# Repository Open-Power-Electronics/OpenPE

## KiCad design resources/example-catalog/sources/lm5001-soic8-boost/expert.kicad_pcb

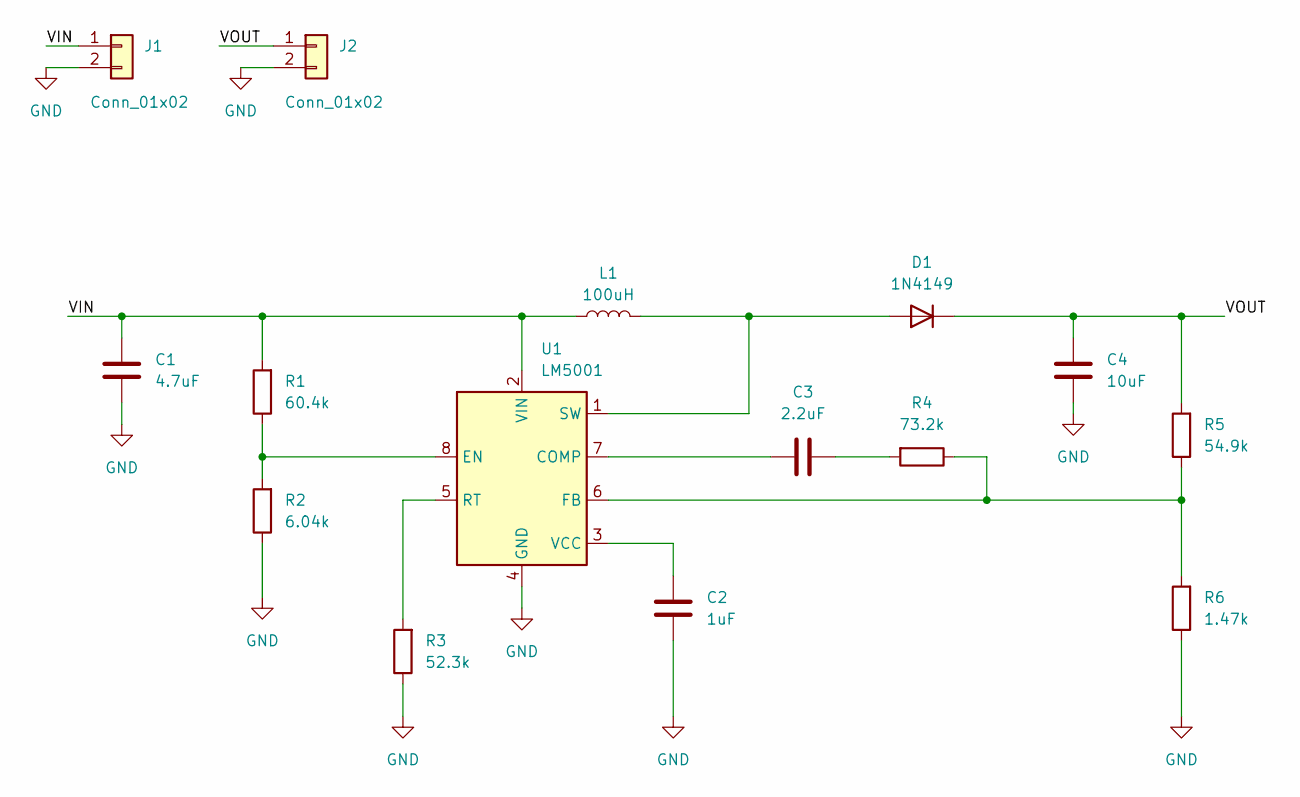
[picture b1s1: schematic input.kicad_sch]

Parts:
C1: 4.7uF; C_1206_3216Metric
C2: 1uF; C_0603_1608Metric
C3: 2.2uF; C_0603_1608Metric
C4: 10uF; C_1206_3216Metric
D1: 1N4149; D_DO-35_SOD27_P7.62mm_Horizontal
J1, J2: Conn_01x02; TerminalBlock_Phoenix_PT-1,5-2-3.5-H_1x02_P3.50mm_Horizontal
L1: 100uH; L_TDK_SLF7055
R1: 60.4k; R_0603_1608Metric
R2: 6.04k; R_0603_1608Metric
R3: 52.3k; R_0603_1608Metric
R4: 73.2k; R_0603_1608Metric
R5: 54.9k; R_0603_1608Metric
R6: 1.47k; R_0603_1608Metric
U1: LM5001; SOIC-8_3.9x4.9mm_P1.27mm

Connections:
/VIN: C1.1, J1.1, L1.1, R1.2, U1.2 (VIN)
/VOUT: C4.1, D1.1 (K), J2.1, R5.2
GND: C1.2, C2.1, C4.2, J1.2, J2.2, R2.1, R3.1, R6.1, U1.4 (GND)
unnamed: C3.1, R4.2
unnamed: D1.2 (A), L1.2, U1.1 (SW)
unnamed: C3.2, U1.7 (COMP)
unnamed: R1.1, R2.2, U1.8 (EN)
unnamed: R4.1, R5.1, R6.2, U1.6 (FB)
unnamed: R3.2, U1.5 (RT)
unnamed: C2.2, U1.3 (VCC)

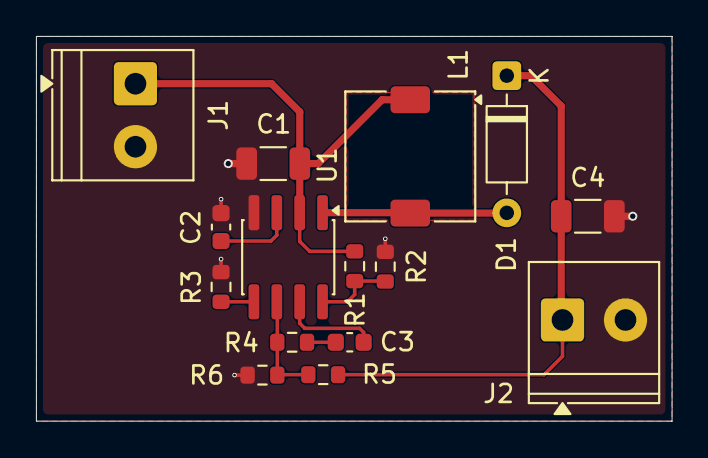
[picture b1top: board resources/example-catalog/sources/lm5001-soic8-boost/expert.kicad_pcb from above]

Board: 2 copper layers, 35.3 x 21.4 mm, 15 parts (0 on the bottom side), 10 nets.

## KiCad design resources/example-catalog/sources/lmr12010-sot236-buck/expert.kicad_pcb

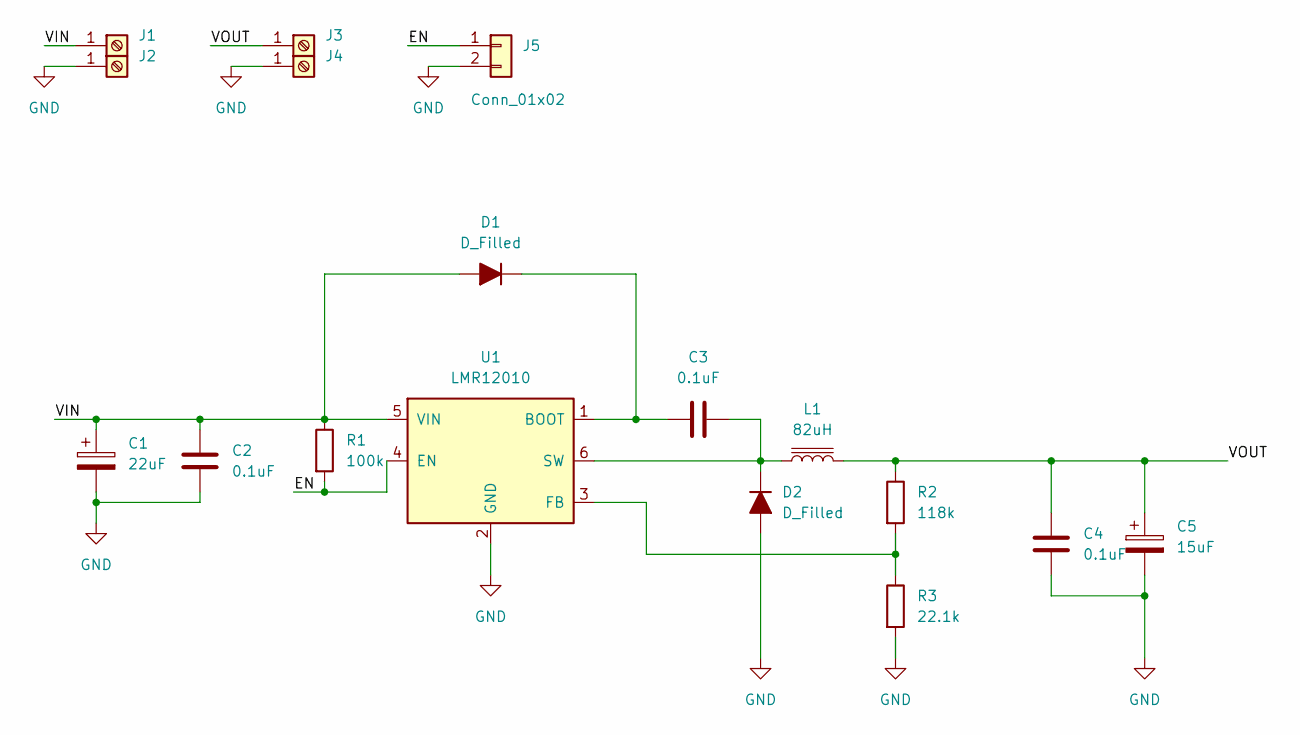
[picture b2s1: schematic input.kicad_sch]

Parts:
C1: 22uF; CP_Elec_6.3x5.3
C2, C4: 0.1uF; C_0805_2012Metric
C3: 0.1uF; C_0603_1608Metric
C5: 15uF; CP_Elec_6.3x5.3
D1: D_Filled; D_SOD-123
D2: D_Filled; D_SMA
J1, J2, J3, J4: Screw_Terminal_01x01; Wuerth_REDCUBE-THR_WP-THRSH_74651174_THR
J5: Conn_01x02; PinSocket_1x02_P2.00mm_Vertical
L1: 82uH; L_APV_APH0530
R1: 100k; R_0603_1608Metric
R2: 118k; R_0603_1608Metric
R3: 22.1k; R_0603_1608Metric
U1: LMR12010; SOT-23-6

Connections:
/EN: J5.1, R1.2, U1.4 (EN)
/VIN: C1.1, C2.2, D1.2 (A), J1.1 (Pin_1_1), R1.1, U1.5 (VIN)
/VOUT: C4.2, C5.1, J3.1 (Pin_1_1), L1.1, R2.1
GND: C1.2, C2.1, C4.1, C5.2, D2.2 (A), J2.1 (Pin_1_1), J4.1 (Pin_1_1), J5.2, R3.2, U1.2 (GND)
unnamed: C3.1, D1.1 (K), U1.1 (BOOT)
unnamed: C3.2, D2.1 (K), L1.2, U1.6 (SW)
unnamed: R2.2, R3.1, U1.3 (FB)

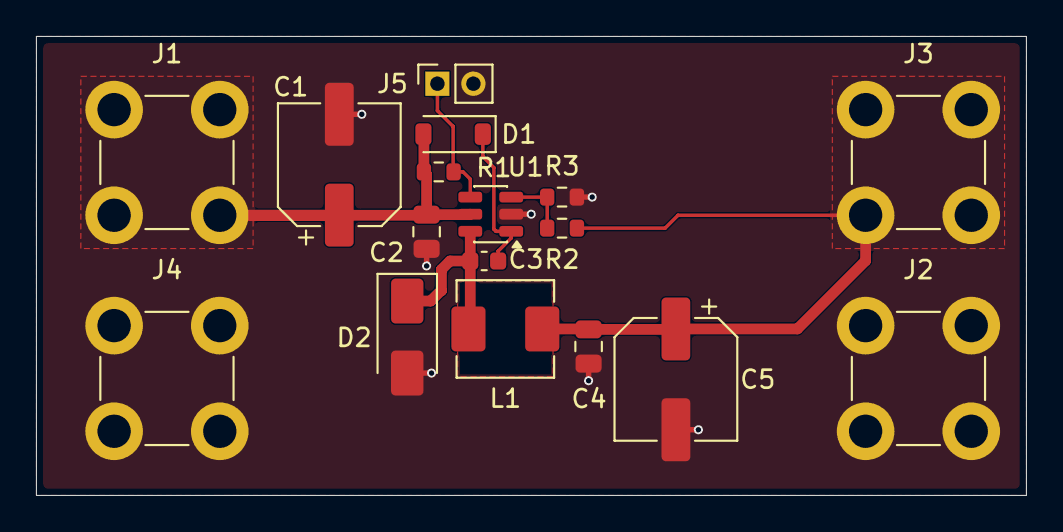
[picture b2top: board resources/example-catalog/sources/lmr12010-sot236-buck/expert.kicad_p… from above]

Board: 2 copper layers, 55.0 x 25.5 mm, 17 parts (0 on the bottom side), 7 nets.

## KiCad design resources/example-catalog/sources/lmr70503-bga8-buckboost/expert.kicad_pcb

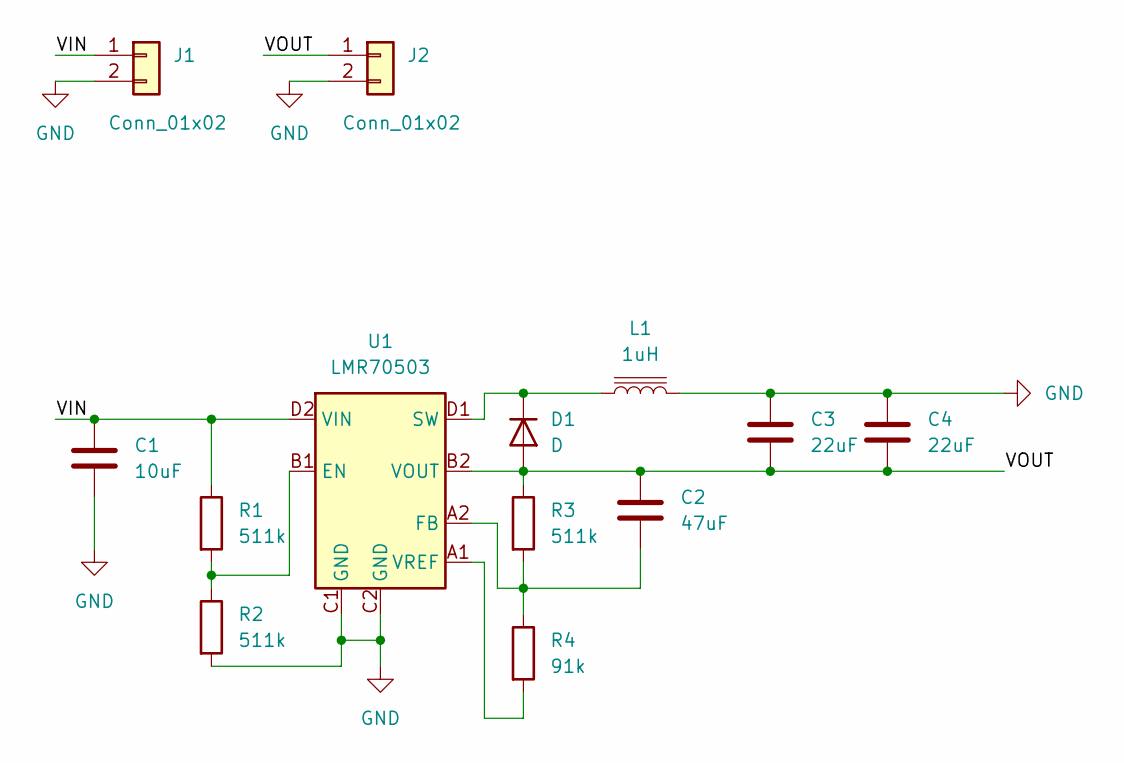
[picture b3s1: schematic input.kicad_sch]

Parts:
C1: 10uF; C_0805_2012Metric
C2: 47uF; C_0402_1005Metric
C3, C4: 22uF; C_0805_2012Metric
D1: D; D_MicroMELF
J1, J2: Conn_01x02; PinHeader_1x02_P1.27mm_Horizontal
L1: 1uH; L_Wurth_WE-LQSH-2512
R1, R2, R3: 511k; R_0402_1005Metric
R4: 91k; R_0402_1005Metric
U1: LMR70503; Texas_DSBGA-8_0.9x1.9mm_Layout2x4_P0.5mm

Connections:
/VIN: C1.1, J1.1, R1.1, U1.D2 (VIN)
/VOUT: C2.2, C3.1, C4.1, D1.2 (A), J2.1, R3.1, U1.B2 (VOUT)
GND: C1.2, C3.2, C4.2, J1.2, J2.2, L1.2, R2.2, U1.C1 (GND), U1.C2 (GND)
unnamed: D1.1 (K), L1.1, U1.D1 (SW)
unnamed: R1.2, R2.1, U1.B1 (EN)
unnamed: C2.1, R3.2, R4.1, U1.A2 (FB)
unnamed: R4.2, U1.A1 (VREF)

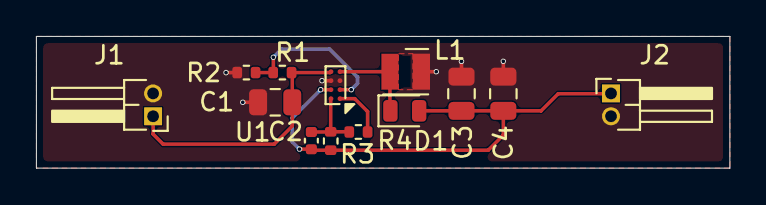
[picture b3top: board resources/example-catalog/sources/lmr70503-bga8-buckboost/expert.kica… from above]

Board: 2 copper layers, 38.5 x 7.3 mm, 13 parts (0 on the bottom side), 7 nets.

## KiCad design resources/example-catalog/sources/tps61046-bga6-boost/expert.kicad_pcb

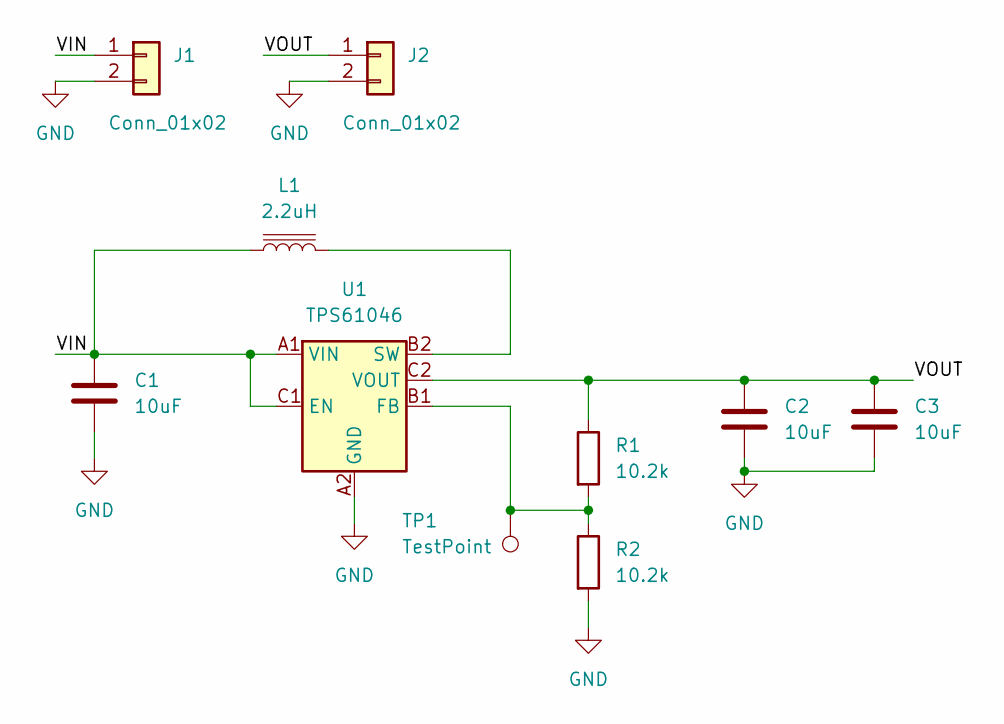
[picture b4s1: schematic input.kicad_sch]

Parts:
C1, C2, C3: 10uF; C_0603_1608Metric
J1, J2: Conn_01x02; PinHeader_1x02_P2.00mm_Vertical
L1: 2.2uH; L_Wurth_WE-LQSH-2010
R1, R2: 10.2k; R_0603_1608Metric
TP1: TestPoint; TestPoint_Keystone_5005-5009_Compact
U1: TPS61046; Texas_DSBGA-6_0.855x1.255mm_Layout2x3_P0.4mm_LevelC

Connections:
/VIN: C1.1, J1.1, L1.1, U1.A1 (VIN), U1.C1 (EN)
/VOUT: C2.2, C3.2, J2.1, R1.1, U1.C2 (VOUT)
GND: C1.2, C2.1, C3.1, J1.2, J2.2, R2.2, U1.A2 (GND)
unnamed: R1.2, R2.1, TP1.1 (1_1), U1.B1 (FB)
unnamed: L1.2, U1.B2 (SW)

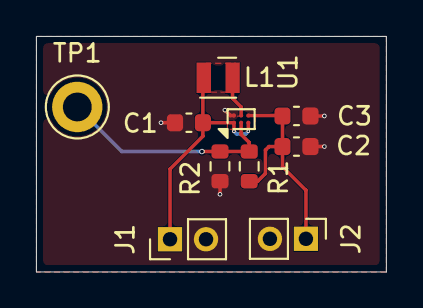
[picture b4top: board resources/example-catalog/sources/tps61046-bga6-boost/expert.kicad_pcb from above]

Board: 2 copper layers, 19.4 x 13.1 mm, 10 parts (0 on the bottom side), 5 nets.

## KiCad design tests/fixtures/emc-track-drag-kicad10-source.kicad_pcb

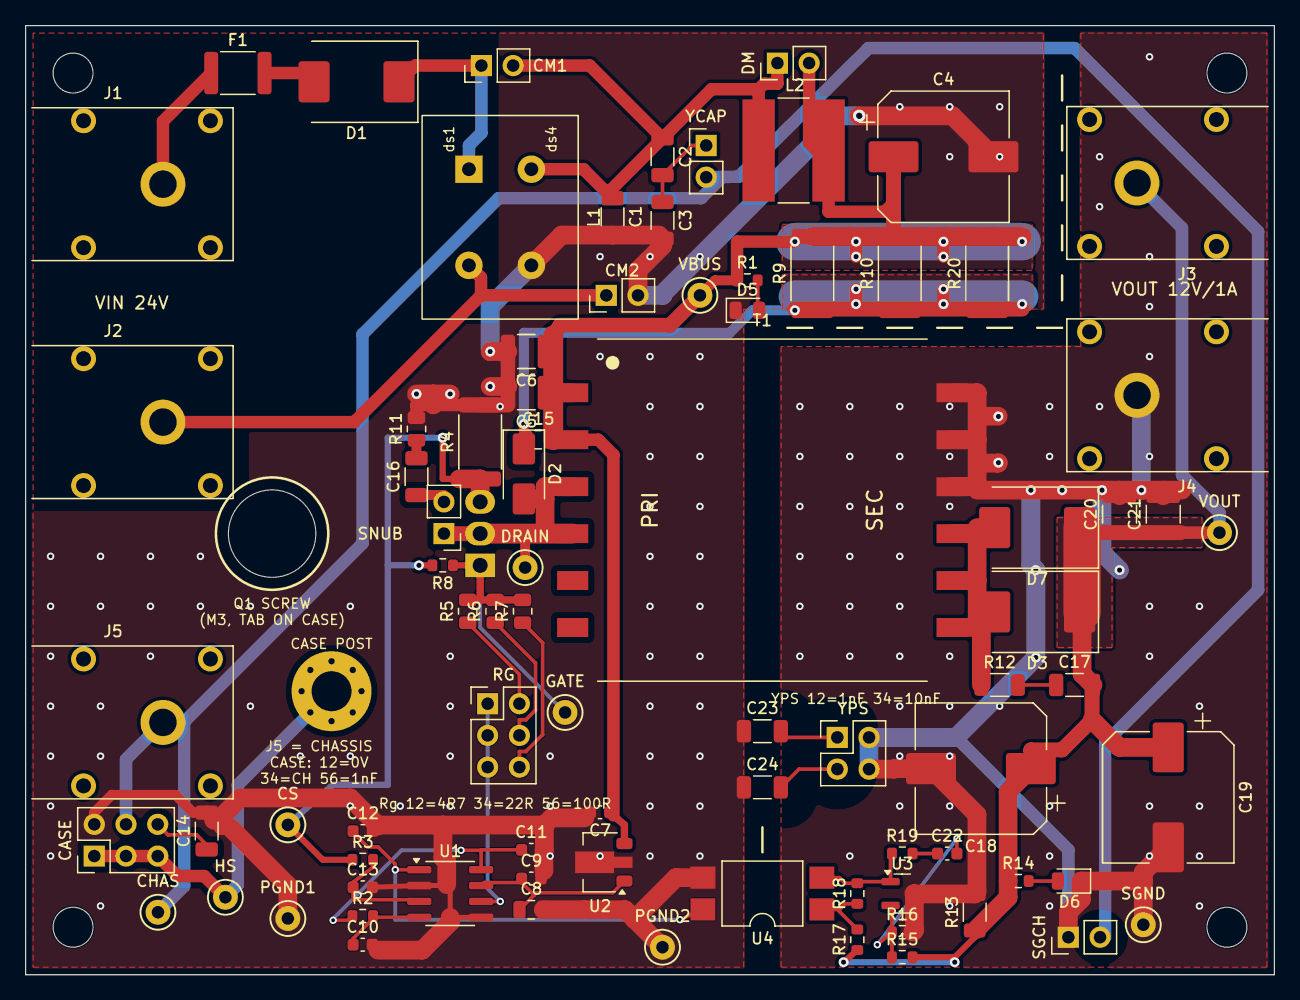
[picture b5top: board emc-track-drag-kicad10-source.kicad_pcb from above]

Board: 2 copper layers, 100.0 x 76.0 mm, 90 parts (0 on the bottom side), 38 nets.

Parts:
C1: 1u; C_1206_3216Metric
C2, C3, C24: 10n; C_1206_3216Metric
C4: 100u; CP_Elec_10x10
C5, C6: 4.7u; C_1210_3225Metric
C7, C9, C11: 100n; C_0603_1608Metric
C8: 10u; C_0805_2012Metric
C10, C12: 1n; C_0603_1608Metric
C13: 220p; C_0603_1608Metric
C14, C23: 1n; C_1206_3216Metric
C15: 22n; C_0805_2012Metric
C16, C17: 100p; C_1206_3216Metric
C18, C19: 470u; CP_Elec_10x10
C20, C21: 22u; C_1210_3225Metric
C22: 47n; C_0603_1608Metric
CASE: Case select; PinHeader_2x03_P2.54mm_Vertical
CHAS: CHASSIS; TestPoint_Keystone_5000-5004_Miniature
CM1: CM bypass +; PinHeader_1x02_P2.54mm_Vertical
CM2: CM bypass -; PinHeader_1x02_P2.54mm_Vertical
CS: CSRAW; TestPoint_Keystone_5000-5004_Miniature
D1, D3, D7: SS510C; D_SMC
D2: ES2D; D_SMA
D5: RED; LED_0805_2012Metric
D6: GREEN; LED_0805_2012Metric
DM: DM bypass; PinHeader_1x02_P2.54mm_Vertical
DRAIN: SW; TestPoint_Keystone_5000-5004_Miniature
F1: 2A/30V PTC; Fuse_1812_4532Metric
GATE: GATE; TestPoint_Keystone_5000-5004_Miniature
HS: HS; TestPoint_Keystone_5000-5004_Miniature
J1: VIN+ 24V; Jack_4mm_RA_Cliff_FCR7350
J2: VIN- 0V; Jack_4mm_RA_Cliff_FCR7350
J3: VOUT +12V; Jack_4mm_RA_Cliff_FCR7350
J4: VOUT 0V; Jack_4mm_RA_Cliff_FCR7350
J5: CHASSIS; Jack_4mm_RA_Cliff_FCR7350
L1: 2.2mH; L_CommonMode_Wuerth_WE-CMB-S_744822222
L2: 10uH; L_Bourns-SRN8040_8x8.15mm
MECH1: Case_UChannel_revD
MECH2: Cover_PMMA_revD
MH1, MH2, MH3, MH4: M3; MountingHole_3.2mm_M3
MH5: M3 CASE; MountingHole_3.2mm_M3_Pad_Via
PGND1, PGND2: PGND; TestPoint_Keystone_5000-5004_Miniature
Q1: IRF520NPBF; TO-220-3_BottomMount_CaseHeatsink
R1, R8, R16, R19: 10k; R_0603_1608Metric
R2: 5.6k; R_0603_1608Metric
R3, R17, R18: 1k; R_0603_1608Metric
R4: 0.15R; R_2512_6332Metric
R5: 4.7R; R_0805_2012Metric
R6: 22R; R_0805_2012Metric
R7: 100R; R_0805_2012Metric
R9, R10, R20: 4.7k; R_2512_6332Metric
R11: 47R; R_0805_2012Metric
R12: 10R; R_1206_3216Metric
R13: 1k; R_1206_3216Metric
R14: 4.7k; R_0603_1608Metric
R15: 39k; R_0603_1608Metric
RG: Rg select; PinHeader_2x03_P2.54mm_Vertical
SGCH: SGND to chassis; PinHeader_1x02_P2.54mm_Vertical
SGND: SGND; TestPoint_Keystone_5000-5004_Miniature
SNUB: RC snubber on; PinHeader_1x02_P2.54mm_Vertical
T1: 750311591; Wurth_750311591_EFD25
U1: UC3845B; SOIC-8_3.9x4.9mm_P1.27mm
U2: L78L12ACUTR; SOT-89-3
U3: TL431AIDBZR; SOT-23
U4: LTV-817S; SMDIP-4_W9.53mm
VBUS: VBUS; TestPoint_Keystone_5000-5004_Miniature
VOUT: VOUT; TestPoint_Keystone_5000-5004_Miniature
YCAP: Y-caps to chassis; PinHeader_1x02_P2.54mm_Vertical
YPS: Pri-sec Y-cap; PinHeader_2x02_P2.54mm_Vertical

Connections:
CHASSIS: CASE.4, CHAS.1, J5.1, SGCH.2, YCAP.2
CLAMP: C15.1, D2.1, R9.1, R10.1, R20.1
COMP: C12.1, U1.1, U4.4
CSRAW: CS.1, Q1.3, R3.1, R4.1, R8.2
DRV: RG.1, RG.3, RG.5, U1.6
FBC: C22.1, R19.2
FBK: R18.2, R19.1, U3.1, U4.2
FP: C1.1, C2.1, CM1.2, DM.1, L1.2, L2.1
GATE: GATE.1, Q1.1, R5.2, R6.2, R7.2, R8.1
HS: CASE.1, CASE.3, CASE.5, HS.1, MH5.1
HSY: C14.1, CASE.6
ISENSE: C13.1, R3.2, U1.3
LEDP: D5.2, R1.2
LEDS: D6.2, R14.2
OPTA: R17.2, R18.1, U4.1
PGND: C1.2, C3.2, C4.2, C5.2, C6.2, C7.2, C8.2, C9.2, C10.2, C11.2, C12.2, C13.2, C14.2, C23.1, C24.1, CASE.2, CM2.2, D5.1, L1.4, PGND1.1, PGND2.1, R4.2, R11.2, U1.2, U1.5, U2.2, U4.3
PSY1: C23.2, YPS.1
PSY2: C24.2, YPS.3
REF: C22.2, R15.2, R16.1, U3.2
RG1: R5.1, RG.2
RG2: R6.1, RG.4
RG3: R7.1, RG.6
RTCT: C10.1, R2.2, U1.4
SEC: D3.2, D7.2, R12.1, T1.7, T1.8, T1.9
SGND: C18.2, C19.2, C20.2, C21.2, D6.1, J4.1, R13.2, R16.2, SGCH.1, SGND.1, T1.10, T1.11, T1.12, U3.3, YPS.2, YPS.4
SNA: C16.1, SNUB.2
SNB: C16.2, R11.1
SNS: C17.1, R12.2
SW: D2.2, DRAIN.1, Q1.2, SNUB.1, T1.3, T1.4
VBUS: C4.1, C5.1, C6.1, C7.1, C15.2, DM.2, L2.2, R1.1, R9.2, R10.2, R20.2, T1.1, T1.2, U2.3, VBUS.1
VCC: C8.1, C9.1, U1.7, U2.1
VD: CM1.1, D1.1, L1.1
VF: D1.2, F1.2
VIN_N: CM2.1, J2.1, L1.3
VIN_P: F1.1, J1.1
VOUT: C17.2, C18.1, C19.1, C20.1, C21.1, D3.1, D7.1, J3.1, R13.1, R14.1, R15.1, R17.1, VOUT.1
VREF: C11.1, R2.1, U1.8
YN: C2.2, C3.1, YCAP.1

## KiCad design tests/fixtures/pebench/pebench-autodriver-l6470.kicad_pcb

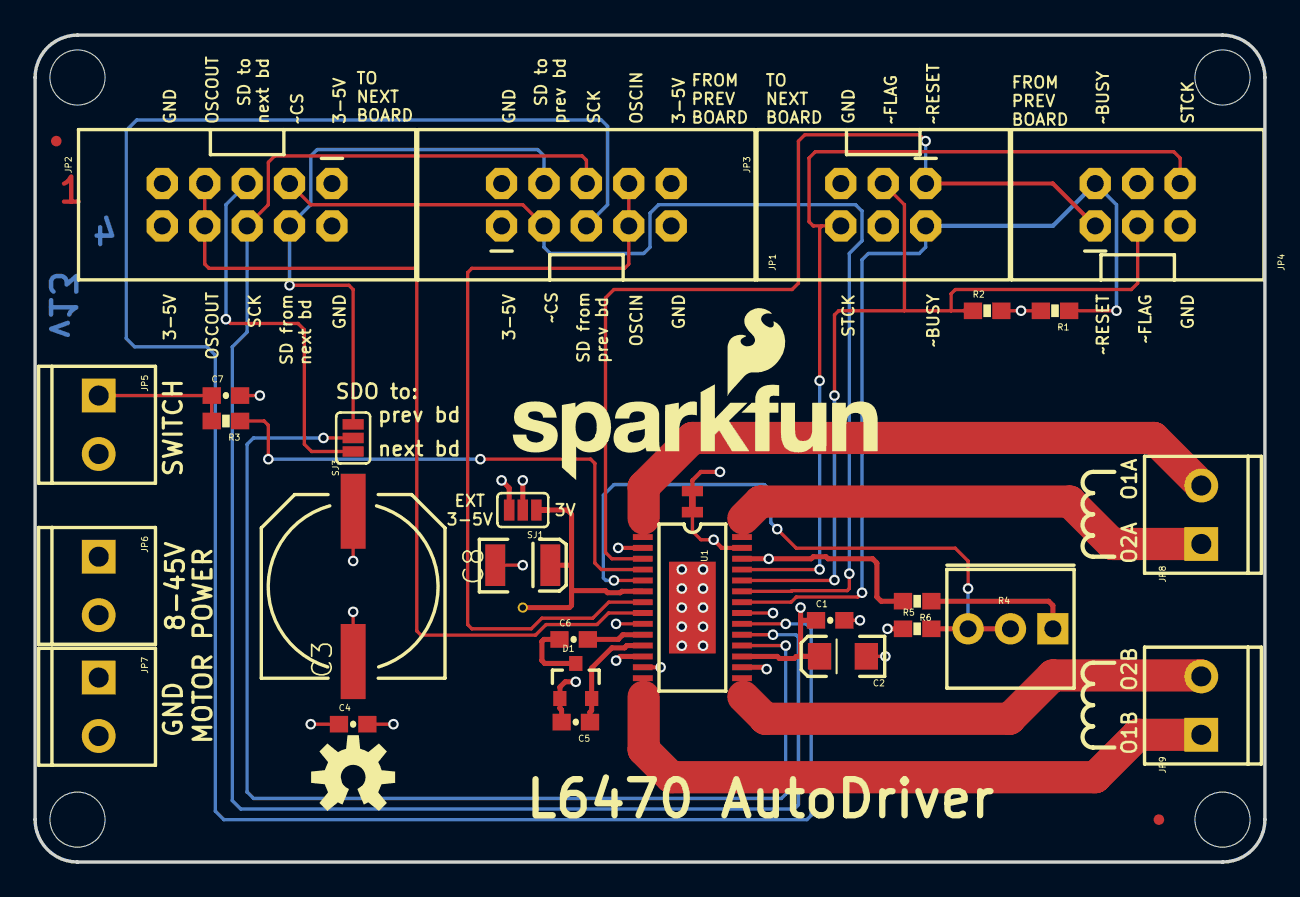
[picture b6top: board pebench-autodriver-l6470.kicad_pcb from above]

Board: 4 copper layers, 73.7 x 49.5 mm, 39 parts (0 on the bottom side), 29 nets.

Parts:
C1: 0.1uF; 0603-CAP
C2: 10uF; EIA3216
C3: 100uF; NIC_10X10.5_CAP
C4, C5: 0.22uF; 0603-CAP
C6, C7: 10nF; 0603-CAP
C8: 47uF; EIA3528
D1: BAV99; SOT23-3
FID1, FID2: FIDUCIALUFIDUCIAL; MICRO-FIDUCIAL
FRAME1: FRAME-LETTER; CREATIVE_COMMONS
JP1, JP2: M05X2SHD; 2X5-SHROUDED
JP3, JP4: M03X2SHROUD; 2X3-SHROUDED
JP5, JP6, JP7, JP8, JP9: M023.5MM; SCREWTERMINAL-3.5MM-2
LOGO1: OSHW-LOGOM; OSHW-LOGO-M
LOGO2: SFE_LOGO_NAME_FLAME.2_INCH; SFE_LOGO_NAME_FLAME_.2
R1, R2: 10k; 0603-RES
R3: 100; 0603-RES
R4: 200k; 3362U
R5: 8.2k; 0603-RES
R6: 33k; 0603-RES
SJ1, SJ3: JUMPER-PAD-3-2OF3_NC_BY_PASTE; PAD-JUMPER-3-2OF3_NC_BY_PASTE_YES_SILK_FULL_BOX
SJ2: 2PT_GND_TIE
STANDOFF1, STANDOFF2, STANDOFF3, STANDOFF4: STAND-OFF
TP1: TEST-POINTTP_15TH_THRU; TP_15TH
U1: L6470; HTSSOP28
U$4: FOUR_LAYER_WARNING

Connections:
3.3V: C8.A, SJ1.1, TP1.P$1, U1.6
5V: JP1.1, JP1.10, JP2.1, JP2.10, SJ1.3
ADC: R4.P$2, R4.P$3, R5.2, U1.5
BUSYN: JP3.2, JP4.2, R1.1, U1.22
CP_HIGH: C6.1, D1.3
CSN: JP1.3, JP2.3, U1.23
D_RETURN: JP1.4, JP2.4, SJ3.3
FLAGN: JP3.3, JP4.3, R2.1, U1.24
GND: C1.2, C2.C, C7.2, C8.C, JP1.2, JP1.9, JP2.2, JP2.9, JP3.5, JP4.5, JP5.2, R5.1, SJ2.P$1, U1.9, U1.21
unnamed: R4.P$1, R6.1
OSCIN: JP1.7, JP1.8, U1.7
OSCOUT: JP2.7, JP2.8, U1.8
OUT1A: JP8.2, U1.1
OUT1B: JP9.1, U1.14
OUT2A: JP8.1, U1.28
OUT2B: JP9.2, U1.15
PGND: C3.-, C4.2, JP7.1, JP7.2, SJ2.P$2, U1.13, U1.27, U1.29
RESETN: JP3.1, JP4.1, U1.3
SCK: JP1.6, JP2.6, U1.19
SDI: JP1.5, U1.20
SDO: SJ3.2, U1.18
SDO_DOWNSTREAM: JP2.5, SJ3.1
STCK: JP3.6, JP4.6, U1.25
SWITCH_INPUT: C7.1, JP5.1, R3.2
SWITCH_SIG: R3.1, U1.4
VLOGIC: C1.1, C2.A, R1.2, R2.2, SJ1.2, U1.17
VS: C3.+, C4.1, C5.2, D1.1, JP6.1, JP6.2, R6.2, U1.2, U1.12, U1.16, U1.26
V_BOOT: C5.1, D1.2, U1.11
V_CP: C6.2, U1.10

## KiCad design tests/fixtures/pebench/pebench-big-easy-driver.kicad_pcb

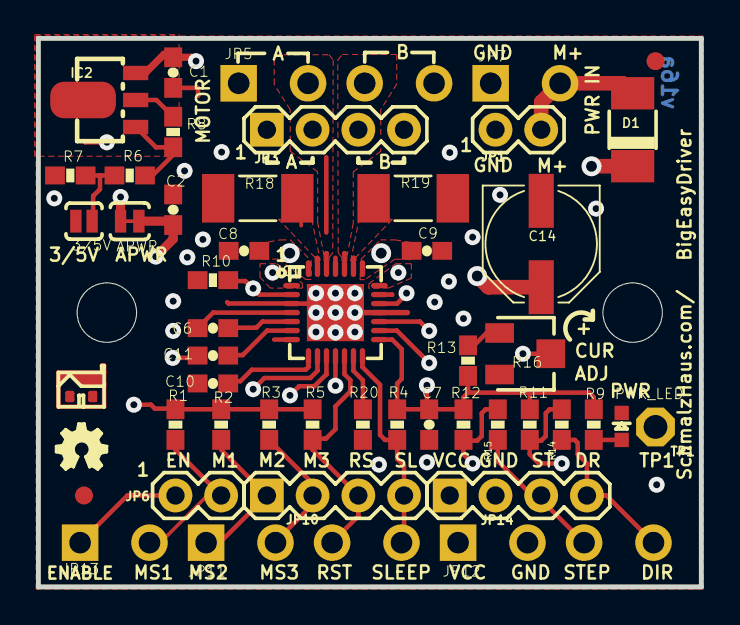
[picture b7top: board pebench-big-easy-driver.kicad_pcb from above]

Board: 4 copper layers, 36.8 x 30.5 mm, 56 parts (1 on the bottom side), 34 nets.

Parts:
3/5V: SOLDERJUMPERNO; SJ_2S-NO
APWR: SOLDERJUMPERTRACE; SJ_2S-TRACE
C1: .1uF; 0603-CAP
C2: 1uF; 0603-CAP
C6, C7, C8, C9, C11: .1uf; 0603-CAP
C10: .22uF; 0603-CAP
C14: 47uF; PANASONIC_D
D1: B340A-13-F; DO-214AC
FID1, FID2: FIDUCIAL1X2; FIDUCIAL-1X2
FRAME1: FRAME-LETTER; CREATIVE_COMMONS
IC1: A4988ALT1; QFN-28-5MM_ALT1
IC2: LM317L; SCHMALZHAUS_SOT89
JP1, JP6: M02PTH; 1X02
JP3, JP10, JP14: M04PTH; 1X04
JP5, JP11, JP12: M04SCREW_LOCK; SCREWTERMINAL-3.5MM-4_LOCK
JP7, JP13: M023.5MM_LOCK; SCREWTERMINAL-3.5MM-2_LOCK
JP8, JP9: STAND-OFF
LOGO1: OSHW_LOGO_FILLX0100-NT; OSHW_FILLX100_NOTEXT
PWR_LED: YELLOW; LED-0603
R1, R2, R3, R4, R5, R10, R11, R12, R20: 20K; 0603-RES
R6: 390; 0603-RES
R7: 330; 0603-RES
R8: 240; 0603-RES
R9, R14, R15: 1K; 0603-RES
R13: 8.2K; 0603-RES
R16: 10K; TRIMPOT-3MM-2
R18, R19: .11; R2010
TP1: TPPAD1-13; P1-13
U$1: SCHMALZHAUS_SMALL
U$2: LOGO-SFENEW; SFE-NEW-WEBLOGO
U$3, U$4, U$5: PAD; PAD-0.008

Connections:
5V_ALT: APWR.1, IC2.OUT, IC2.OUT@1, R8.2
COILA+: IC1.P$21, JP3.4, JP5.4
COILA-: IC1.P$24, JP3.3, JP5.3
COILB+: IC1.P$1, JP3.1, JP5.1
COILB-: IC1.P$26, JP3.2, JP5.2
CUR_REF: IC1.P$17, R16.2, TP1.TP
DIR: IC1.P$19, R11.1, R14.2
DIR_IN: JP12.4, JP14.4, R14.1
ENABLE: IC1.P$2, JP6.1, JP13.1, R10.1
GND: 3/5V.2, C1.2, C2.2, C7.2, C8.2, C9.2, C10.2, C14.-, IC1.P$3, IC1.P$18, IC1.P$29, JP1.1, JP7.1, JP12.2, JP14.2, PWR_LED.C, R7.1, R10.2, R16.3, R18.1, R19.1, R20.2
MS1: IC1.P$9, JP6.2, JP13.2, R1.1
MS2: IC1.P$10, JP10.1, JP11.1, R2.1
MS3: IC1.P$11, JP10.2, JP11.2, R3.1
unnamed: D1.A, JP1.2, JP7.2
unnamed: PWR_LED.A, R9.1
unnamed: R13.2, R16.1
unnamed: 3/5V.1, R6.1, R7.2
unnamed: IC1.P$7, U$3.P$1
unnamed: IC2.ADJ, R6.2, R8.1
unnamed: IC1.P$20, U$4.P$1
unnamed: C6.1, IC1.P$4
unnamed: C6.2, IC1.P$5
unnamed: IC1.P$25, U$5.P$1
unnamed: IC1.P$13, R20.1
unnamed: C10.1, IC1.P$8
unnamed: C11.1, IC1.P$6
unnamed: IC1.P$27, R18.2
unnamed: IC1.P$23, R19.2
RESET: IC1.P$12, JP10.3, JP11.3, R5.1
SLEEP: IC1.P$14, JP10.4, JP11.4, R4.1
STEP: IC1.P$16, R12.1, R15.2
STEP_IN: JP12.3, JP14.3, R15.1
V+: C1.1, C8.1, C9.1, C11.2, C14.+, D1.C, IC1.P$22, IC1.P$28, IC2.IN
VCC: APWR.2, C2.1, C7.1, IC1.P$15, JP12.1, JP14.1, R1.2, R2.2, R3.2, R4.2, R5.2, R9.2, R11.2, R12.2, R13.1

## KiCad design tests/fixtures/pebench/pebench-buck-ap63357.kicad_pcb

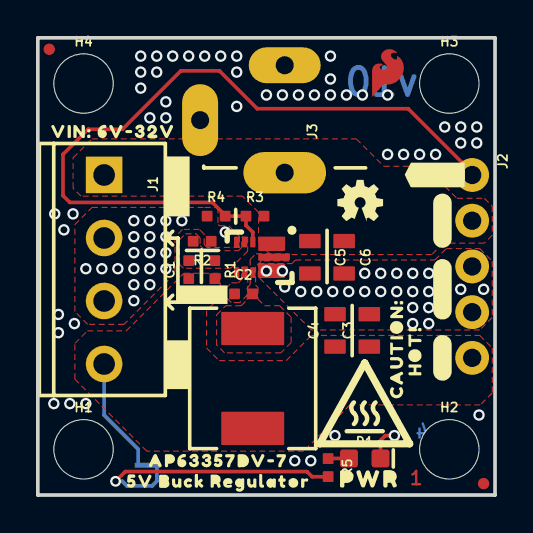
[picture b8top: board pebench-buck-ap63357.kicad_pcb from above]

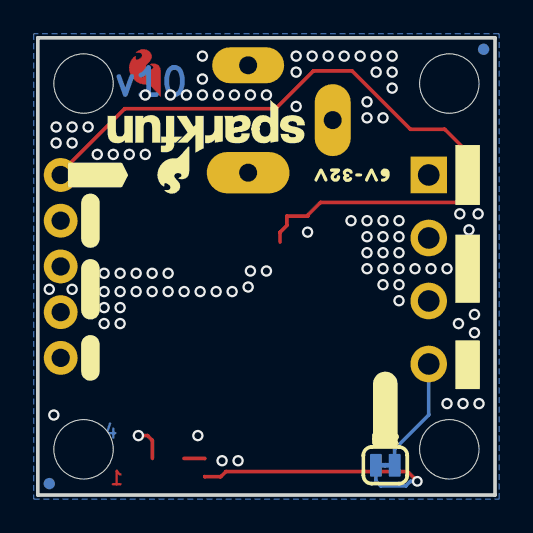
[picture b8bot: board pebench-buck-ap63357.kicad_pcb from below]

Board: 4 copper layers, 25.4 x 25.4 mm, 54 parts (13 on the bottom side), 9 nets.

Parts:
C1: 47pF; 0402-TIGHT
C2: 0.1uF; 0402-TIGHT
C3, C4: 22uF; 0805
C5, C6: 4.7uF; 0805
D1: RED; LED-0603
FD1, FD2, FD3, FD4: FIDUCIALUFIDUCIAL; FIDUCIAL-MICRO
FRAME1: FRAME-LEDGER; CREATIVE_COMMONS
H1, H2, H3, H4: STAND-OFF
J1: CONN_04SCREW; SCREWTERMINAL-3.5MM-4
J2: CONN_05NO_SILK; 1X05_NO_SILK
J3: POWER_JACK; POWER_JACK_PTH_SLOT_NO_OVRHNG_SILK
L1: 6.8UH; 07A7_6U8H
LOGO1: OSHW-LOGOMINI; OSHW-LOGO-MINI
LOGO2: SFE_LOGO_NAME_FLAME.1_INCH; SFE_LOGO_NAME_FLAME_.1
PWR: JUMPER-SMT_2_NC_TRACE_SILK; SMT-JUMPER_2_NC_TRACE_SILK
R1: 220K; 0402-TIGHT
R2: 41.2K; 0402-TIGHT
R3: 93.1k; 0402-TIGHT
R4: 22k; 0402-TIGHT
R5: 2.2k; 0402-TIGHT
U1: AP63357; V-DFN3020-13
U$1: AP63357DV#70
U$2: 5V_BUCK_REGULATOR0
U$3: #5V#4
U$4: #VIN#8
U$5, U$13: #VIN#0
U$6, U$7: #GND#0
U$8, U$19: #EN_#0
U$9: #GND#9
U$10: #5V#10
U$11: 6V#32V10
U$12: HOT##0
U$14, U$24: #5V#0
U$15: #LED_#0
U$16: CAUTION#0
U$17: SFE_LOGO_FLAME_COPPER_EXPOSED_.1
U$18: VIN#_6V#32V0
U$20: PWR0
U$21: #GND#1
U$22: HIGH_TEMP_WARNING
U$23: ORDERING_INSTRUCTIONS
U$26: #VIN#3

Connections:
5V: C1.1, C3.1, C4.1, J1.4, J2.5, L1.P$2, PWR.2, R1.2
EN: J2.1, R3.1, R4.2, U1.P$2
FB: C1.2, R1.1, R2.2, U1.P$3
GND: C3.2, C4.2, C5.2, C6.2, D1.C, J1.2, J1.3, J2.3, J2.4, J3.GND, R2.1, R4.1, U1.P$4, U1.P$8
unnamed: D1.A, R5.1
unnamed: C2.1, U1.P$6
unnamed: PWR.1, R5.2
SW: C2.2, L1.P$1, U1.P$7, U1.P$9
VIN: C5.1, C6.1, J1.1, J2.2, J3.PWR, R3.2, U1.P$1

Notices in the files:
parts and their libraries:
Released under the Creative Commons Attribution Share-Alike 4.0 License
https://creativecommons.org/licenses/by-sa/4.0
Released under the Creative Commons Attribution Share-Alike 3.0 License
http://creativecommons.org/licenses/by-sa/3.0
